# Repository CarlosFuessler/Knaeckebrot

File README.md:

# Knäckebrot

A Corne inspired Split Keboard 

### Features

- Bluetooth
- Personalized Layout
- 128x32 Display

## List of all Parts 
 ```md
 
# For the Assembly

    - PCB
    - 240x Hot Plug Sockets
    - 120x Kahil Choc V2
    - 120x SOD-123
    - 1x Display 128x32
    - 2x Pro Micro NRF52840 | Nice!Nano V2
    - 2x Lipo Batteries (400 mAh)

## Firmware
    
    - Use our ZMK firmware which you can personalize via ZMK Studio
    - Load the Firmware on your controllers via Actions
## Assets
Case designs etc.. are in the Assets folder!

```

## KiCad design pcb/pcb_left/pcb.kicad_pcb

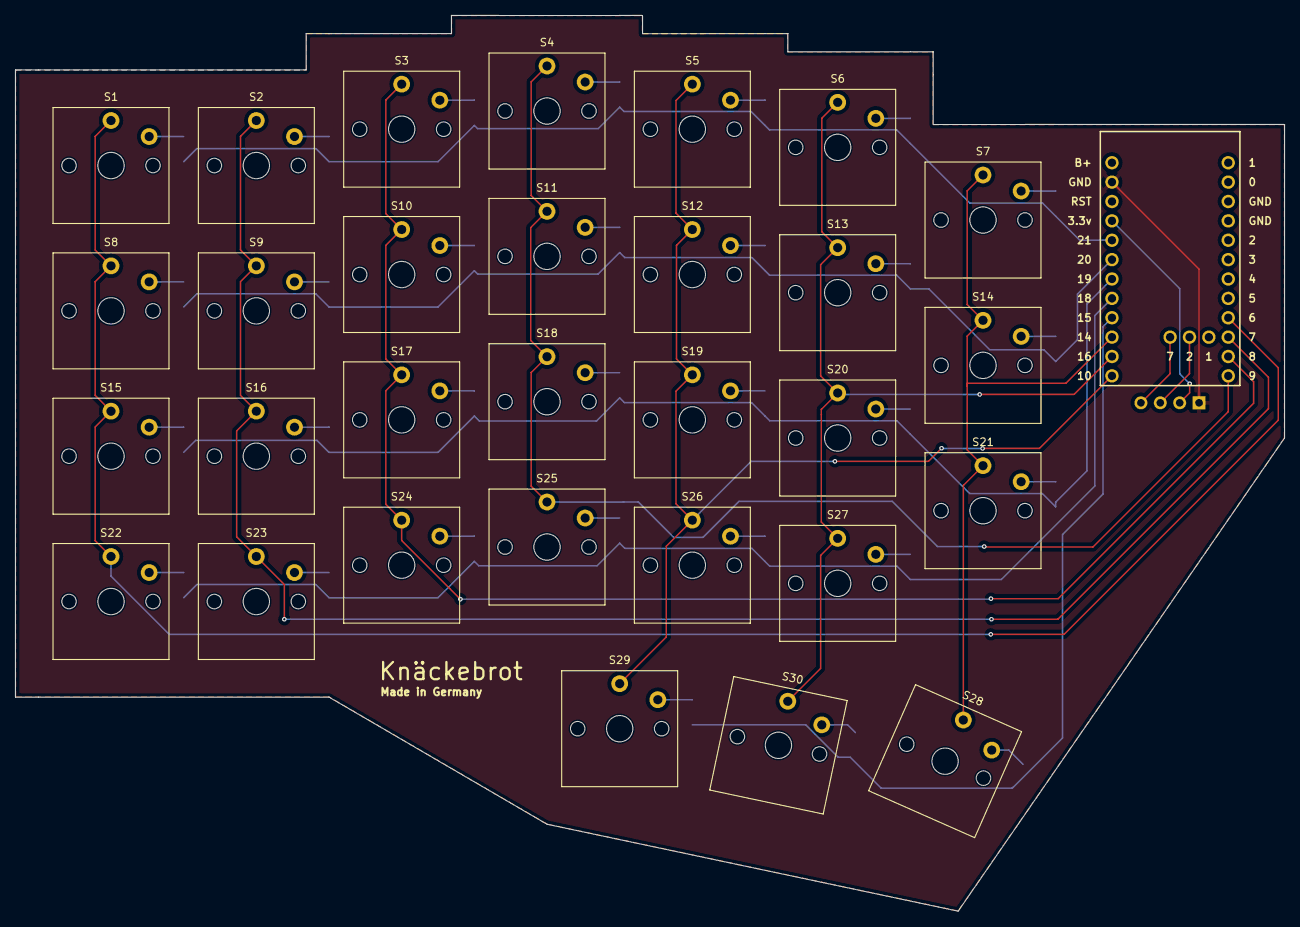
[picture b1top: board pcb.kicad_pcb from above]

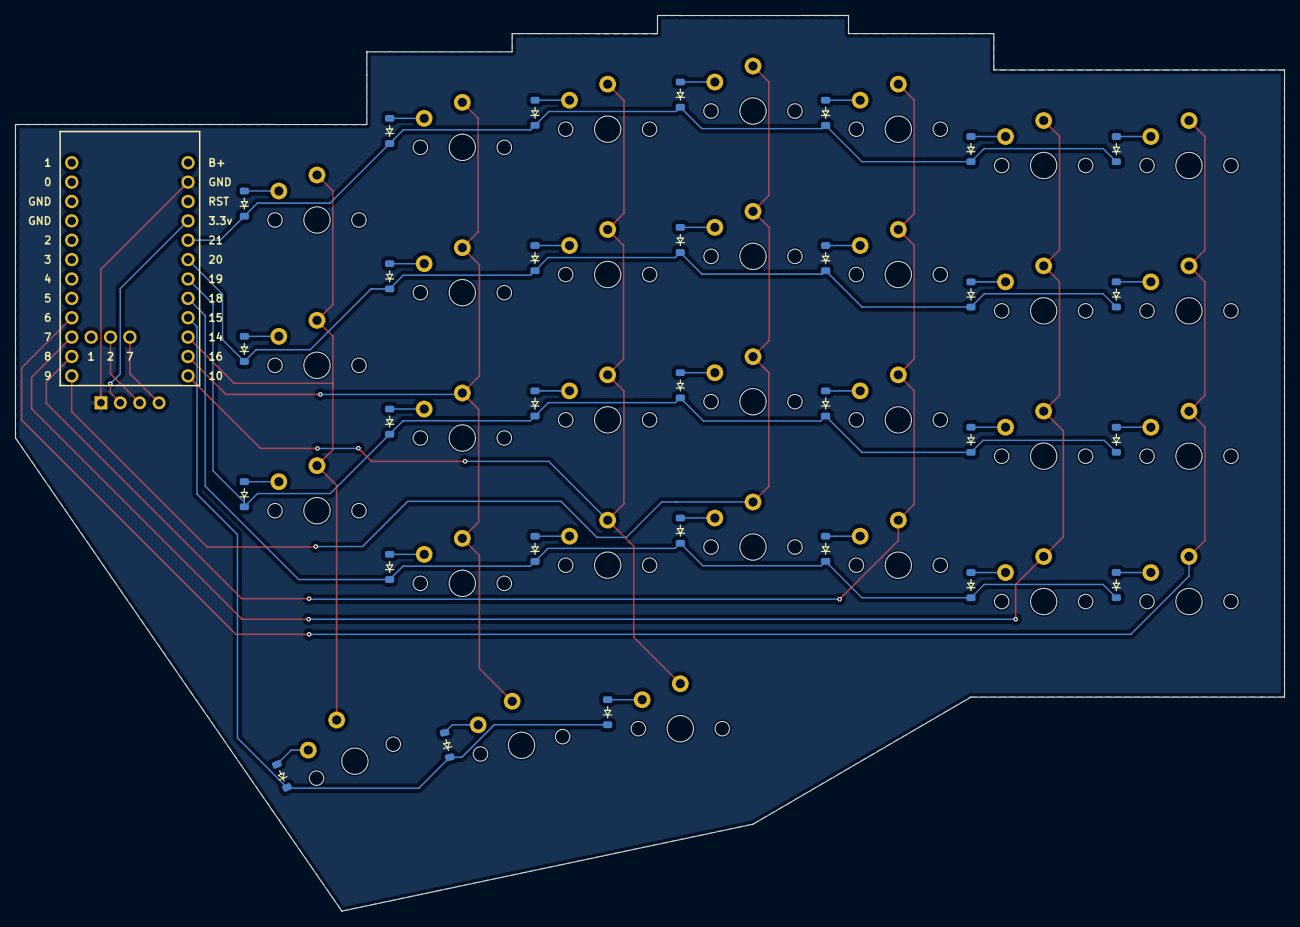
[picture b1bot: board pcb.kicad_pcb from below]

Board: 2 copper layers, 166.4 x 117.4 mm, 62 parts (31 on the bottom side), 46 nets.

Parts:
D1, D2, D3, D4, D5, D6, D7, D8, D9, D10, D11, D12, D13, D14, D15, D16, D17, D18, D19, D20, D21, D22, D23, D24, D25, D26, D27, D28, D29, D30: Diode; Diode_SOD-123
J1: OLED_128x32
S1, S2, S3, S4, S5, S6, S7, S8, S9, S10, S11, S12, S13, S14, S15, S16, S17, S18, S19, S20, S21, S22, S23, S24, S25, S26, S27, S28, S29, S30: Keyswitch; Choc_V1
U1: Nice_Nano_V2

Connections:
GND: J1.1 (GND), U1.23 (GND)
unnamed: D1.2 (A), S1.2
unnamed: D2.2 (A), S2.2
unnamed: D3.2 (A), S3.2
unnamed: D4.2 (A), S4.2
unnamed: D5.2 (A), S5.2
unnamed: D6.2 (A), S6.2
unnamed: D7.2 (A), S7.2
unnamed: D8.2 (A), S8.2
unnamed: D9.2 (A), S9.2
unnamed: D10.2 (A), S10.2
unnamed: D11.2 (A), S11.2
unnamed: D12.2 (A), S12.2
unnamed: D13.2 (A), S13.2
unnamed: D14.2 (A), S14.2
unnamed: D15.2 (A), S15.2
unnamed: D16.2 (A), S16.2
unnamed: D17.2 (A), S17.2
unnamed: D18.2 (A), S18.2
unnamed: D19.2 (A), S19.2
unnamed: D20.2 (A), S20.2
unnamed: D21.2 (A), S21.2
unnamed: D22.2 (A), S22.2
unnamed: D23.2 (A), S23.2
unnamed: D24.2 (A), S24.2
unnamed: D25.2 (A), S25.2
unnamed: D26.2 (A), S26.2
unnamed: D27.2 (A), S27.2
unnamed: D28.2 (A), S28.2
unnamed: D29.2 (A), S29.2
unnamed: D30.2 (A), S30.2
SCL: J1.3 (SCL), U1.26 (2)
SDA: J1.4 (SDA), U1.27 (7)
VCC: J1.2 (VCC), U1.21 (3.3v)
column 0: S1.1, S8.1, S15.1, S22.1, U1.9 (6)
column 1: S2.1, S9.1, S16.1, S23.1, U1.10 (7)
column 2: S3.1, S10.1, S17.1, S24.1, U1.11 (8)
column 3: S4.1, S11.1, S18.1, S25.1, U1.12 (9)
column 4: S5.1, S12.1, S19.1, S26.1, S29.1, U1.13 (10)
column 5: S6.1, S13.1, S20.1, S27.1, S30.1, U1.14 (16)
column 6: S7.1, S14.1, S21.1, S28.1, U1.15 (14)
row 0: D1.1 (K), D2.1 (K), D3.1 (K), D4.1 (K), D5.1 (K), D6.1 (K), D7.1 (K), U1.20 (21)
row 1: D8.1 (K), D9.1 (K), D10.1 (K), D11.1 (K), D12.1 (K), D13.1 (K), D14.1 (K), U1.19 (20)
row 2: D15.1 (K), D16.1 (K), D17.1 (K), D18.1 (K), D19.1 (K), D20.1 (K), D21.1 (K), U1.18 (19)
row 3: D22.1 (K), D23.1 (K), D24.1 (K), D25.1 (K), D26.1 (K), D27.1 (K), U1.17 (18)
row 4: D28.1 (K), D29.1 (K), D30.1 (K), U1.16 (15)

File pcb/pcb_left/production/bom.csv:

Designator,Footprint,Quantity,Value,LCSC Part #
"D1, D10, D11, D12, D13, D14, D15, D16, D17, D18, D19, D2, D20, D21, D22, D23, D24, D25, D26, D27, D28, D29, D3, D30, D4, D5, D6, D7, D8, D9",Diode_SOD-123,30,Diode,
J1,OLED_128x32,1,OLED_128x32,
"S1, S10, S11, S12, S13, S14, S15, S16, S17, S18, S19, S2, S20, S21, S22, S23, S24, S25, S26, S27, S28, S29, S3, S30, S4, S5, S6, S7, S8, S9",Choc_V1,30,Keyswitch,
U1,Nice_Nano_V2,1,Nice_Nano_V2,

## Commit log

2025-08-29 Fix spelling of 'Knäckebrot' in README
2025-08-29 Upadate v1.00
2025-09-05 Update zmk-config submodule pointer
2025-09-08 firmware
2025-09-11 Firmware (new)
2025-09-11 firmware (second)
2025-09-11 update(third)
2025-09-11 firmware(fourth)
2025-09-11 firmware (five)
2025-09-11 gf u ciuktlcvobon
2025-09-11 bvksbneqi
2025-09-11 hvjgi
2025-09-11 idsuvhdtiu
2025-09-11 firmware (six)
2025-09-11 firmware (seven)
2025-09-11 firmware (nine)
2025-09-11 firmware (ten)
2025-09-11 firmware (11)
2025-09-11 firmware (12)
2025-09-11 firmware (13)
